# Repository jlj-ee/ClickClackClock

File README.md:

# ClickClackClock
This was a hobby project to create an impractically loud and large clock constructed from salvaged electromechanical seven-segment flip digits (also known as vane displays). To be slightly less obnoxious, the clock automatically sleeps in dark rooms, and wakes up with the correct time when exposed to light -- great for people who like to wake up with the dawn! 
<!--- The clock can also be put into a countdown/stopwatch mode, appropriate for games, New Year's Eve, the apocalypse, etc. --->

The [flip digits](http://www.scoretronics.com/components/Digits_Brochure.pdf) came from a retired aquatics scoreboard/timing system. The segments change position when current is pulsed through a magnetic coil. 

## Software
__Required dependencies:__

**_More info TBA_**

## CAD Contents
We designed custom 2-layer PCBs for this project using [Eagle](https://www.autodesk.com/products/eagle/overview) and fabbed them using [OSHPark](https://oshpark.com/), with all through-hole components for ease of assembly:
- __clock_driver_board:__ Drives a single digit, and can be daisy-chained together for as many digits as needed.
- __clock_motherboard:__ Slightly larger than the Arduino UNO but with the same microcontroller and pad layout for future shield compatibility. Integrates the standard DS1307 RTC on the board and controls the whole system - digit drivers, buttons, photoresistor, etc.
- __clock_system:__ Schematic that describes the overall system of PCBs and auxiliary components.

## Assembly
The digits are supported in a frame made from MDF. 

**_More info TBA_**

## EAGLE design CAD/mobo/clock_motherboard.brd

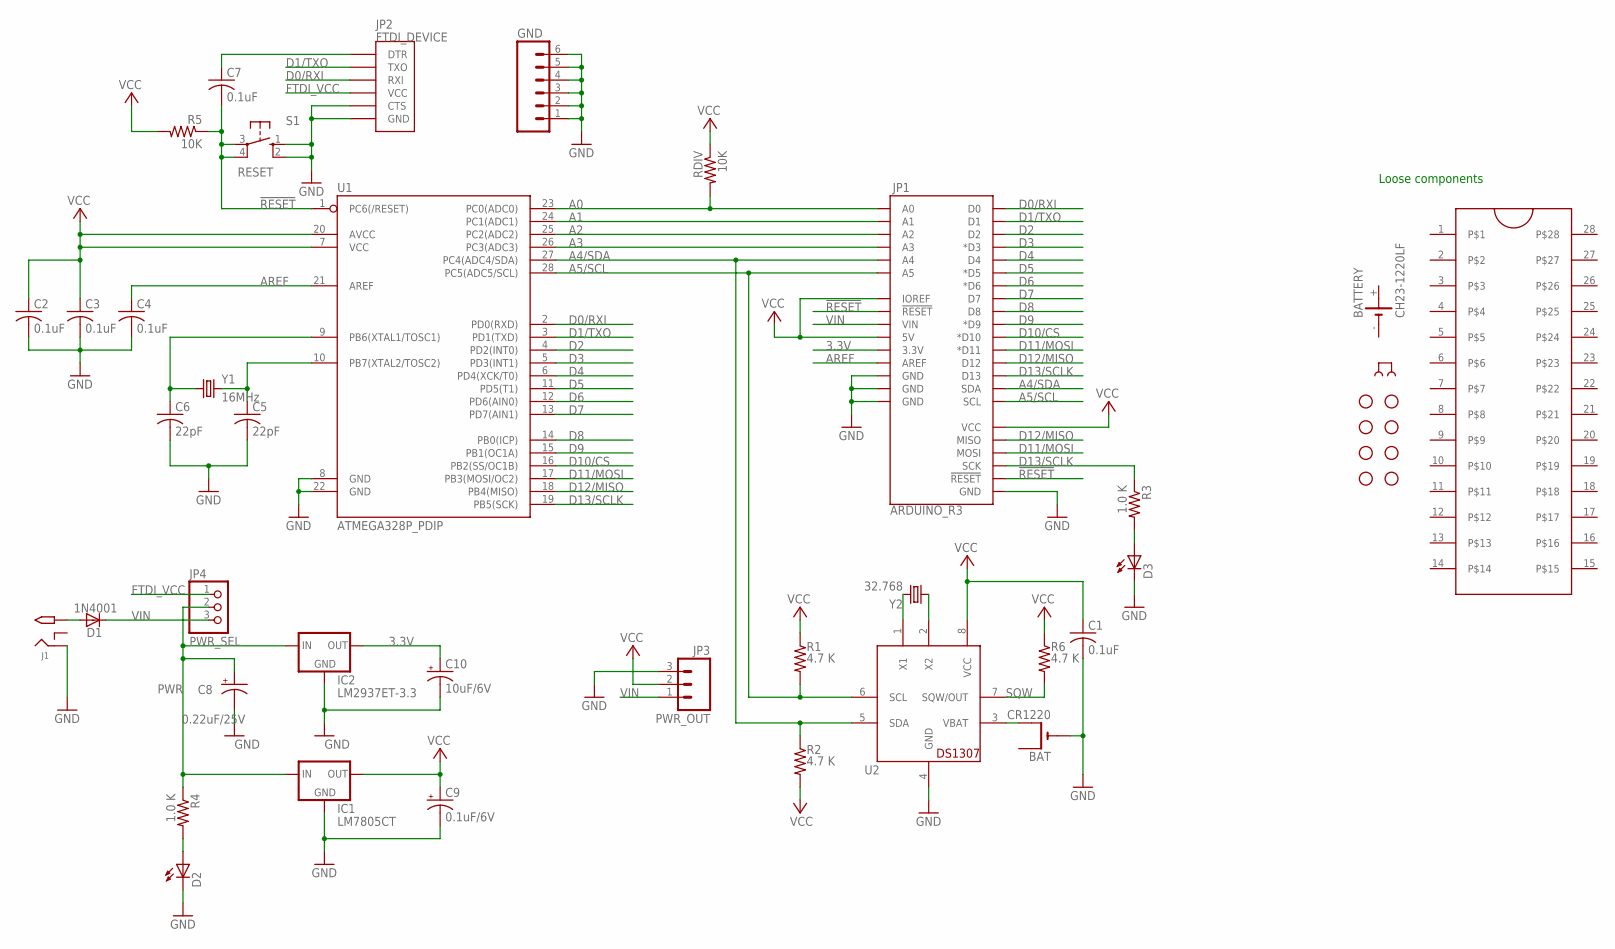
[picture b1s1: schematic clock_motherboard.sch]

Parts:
BAT: CR1220; CR1220-THM; PARTNO 3001
BATTERY: CH23-1220LF; PARTNO CR1220
C1, C2, C3, C4, C7: 0.1uF; C025-025X050; PARTNO 21RZ310-RC
C5, C6: 22pF; C025-025X050; PARTNO K220J15C0GF5TL2
C8: 0.22uF/25V; E2,5-6; PARTNO FG14X7R1H224KNT06
C9: 0.1uF/6V; E2,5-6; PARTNO 21RZ310-RC
C10: 10uF/6V; E2,5-6; PARTNO A758BG106M1EAAE070
D1: 1N4001; DO41-10; PARTNO 1N4001-TP
D2: RED; LED3MM; PARTNO WP7113SRD/D
D3: YELLOW; LED3MM; PARTNO WP7113SYD
GND: M06NO_SILK_FEMALE_PTH; 1X06_NO_SILK
IC1: LM7805CT; 78XXS; PARTNO LM7805CT/NOPB
IC2: LM2937ET-3.3; 78XXS; PARTNO LM2937ET-3.3/NOPB
J1: 2.1MMJACK; PJ-102A; PARTNO PJ-102AH
J2: PWR_SEL; JUMP; PARTNO 382811-8
JP1: ARDUINO_R3
JP2: FTDI_DEVICE; FTDI_DEVICE_SIDE; PARTNO 68000-406HLF
JP3: PWR_OUT; SCREWTERMINAL-3.5MM-3; PARTNO 1546551-3
JP4: PWR_SEL; 1X03; PARTNO 68001-403HLF
R1, R2, R6: 4.7 K; 0207/5V; PARTNO CFR-25JB-52-4K7
R3, R4: 1.0 K; 0207/5V; PARTNO CFR-25JB-52-1K
R5: 10K; 0207/5V; PARTNO CFR-25JB-52-10K
RDIV: 10K; 0207/5V; PARTNO CFR-25JB-52-10K
S1: RESET; B3F-10XX
SOCKET: ZIFSOCKET-28-3ZIFFSOCKET-28-3; DIL28-3-ZIF_SOCKET; PARTNO 4828-3004-CP
STANDOFF1, STANDOFF2, STANDOFF3, STANDOFF4: STAND-OFF; PARTNO 2200
STANDOFF5, STANDOFF6, STANDOFF7, STANDOFF8: STAND-OFF; PARTNO 9900
U1: ATMEGA328P_PDIP; DIL28-3; PARTNO ATMEGA328P-PU
U2: DS1307; DIL08; PARTNO DS1307+
Y1: 16MHz; HC49US; PARTNO HC49US-16.000MABJ-UB
Y2: 32.768; TC38H; PARTNO AB38T-32.768KHZ

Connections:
3.3V: C10.+, IC2.OUT, JP1.3.3V
!RESET: C7.2, JP1.RESET@1 (!RESET!), JP1.RESET@2 (!RESET!), R5.1, S1.3, S1.4 (P1), U1.1 (PC6(/RESET))
A0: JP1.A0, RDIV.2, U1.23 (PC0(ADC0))
A1: JP1.A1, U1.24 (PC1(ADC1))
A2: JP1.A2, U1.25 (PC2(ADC2))
A3: JP1.A3, U1.26 (PC3(ADC3))
A4/SDA: JP1.A4, JP1.SDA, R2.1, U1.27 (PC4(ADC4/SDA)), U2.5 (SDA)
A5/SCL: JP1.A5, JP1.SCL, R1.2, U1.28 (PC5(ADC5/SCL)), U2.6 (SCL)
AREF: C4.1, JP1.AREF, U1.21 (AREF)
D0/RXI: JP1.D0, JP2.P$3 (RXI), U1.2 (PD0(RXD))
D1/TXO: JP1.D1, JP2.P$2 (TXO), U1.3 (PD1(TXD))
D2: JP1.D2, U1.4 (PD2(INT0))
D3: JP1.D3 (*D3), U1.5 (PD3(INT1))
D4: JP1.D4, U1.6 (PD4(XCK/T0))
D5: JP1.D5 (*D5), U1.11 (PD5(T1))
D6: JP1.D6 (*D6), U1.12 (PD6(AIN0))
D7: JP1.D7, U1.13 (PD7(AIN1))
D8: JP1.D8, U1.14 (PB0(ICP))
D9: JP1.D9 (*D9), U1.15 (PB1(OC1A))
D10/CS: JP1.D10 (*D10), U1.16 (PB2(SS/OC1B))
D11/MOSI: JP1.D11 (*D11), JP1.MOSI, U1.17 (PB3(MOSI/OC2))
D12/MISO: JP1.D12, JP1.MISO, U1.18 (PB4(MISO))
D13/SCLK: JP1.D13, JP1.SCK, R3.1, U1.19 (PB5(SCK))
FTDI_VCC: JP2.P$4 (VCC), JP4.1
GND: BAT.-, C1.2, C2.2, C3.2, C4.2, C5.2, C6.2, C8.-, C9.-, C10.-, D2.K (C), D3.K (C), GND.1, GND.2, GND.3, GND.4, GND.5, GND.6, IC1.GND, IC2.GND, J1.RING, JP1.GND@1 (GND), JP1.GND@2 (GND), JP1.GND@3 (GND), JP1.GND@4 (GND), JP2.P$5 (CTS), JP2.P$6 (GND), JP3.3, S1.1 (S), S1.2 (S1), U1.8 (GND), U1.22 (GND), U2.4 (GND)
unnamed: C6.1, U1.9 (PB6(XTAL1/TOSC1)), Y1.1
unnamed: C5.1, U1.10 (PB7(XTAL2/TOSC2)), Y1.2
unnamed: C7.1, JP2.P$1 (DTR)
unnamed: D3.A, R3.2
unnamed: D2.A, R4.2
unnamed: U2.1 (X1), Y2.2
unnamed: U2.2 (X2), Y2.1
unnamed: D1.A, J1.TIP
unnamed: BAT.+2 (+1), U2.3 (VBAT)
PWR: C8.+, IC1.IN, IC2.IN, JP4.2, R4.1
SQW: R6.2, U2.7 (SQW/OUT)
VCC: C1.1, C2.1, C3.1, C9.+, IC1.OUT, JP1.5V, JP1.IOREF, JP1.VCC, JP3.2, R1.1, R2.2, R5.2, R6.1, RDIV.1, U1.7 (VCC), U1.20 (AVCC), U2.8 (VCC)
VIN: D1.C, JP1.VIN, JP3.1, JP4.3

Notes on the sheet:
Loose components

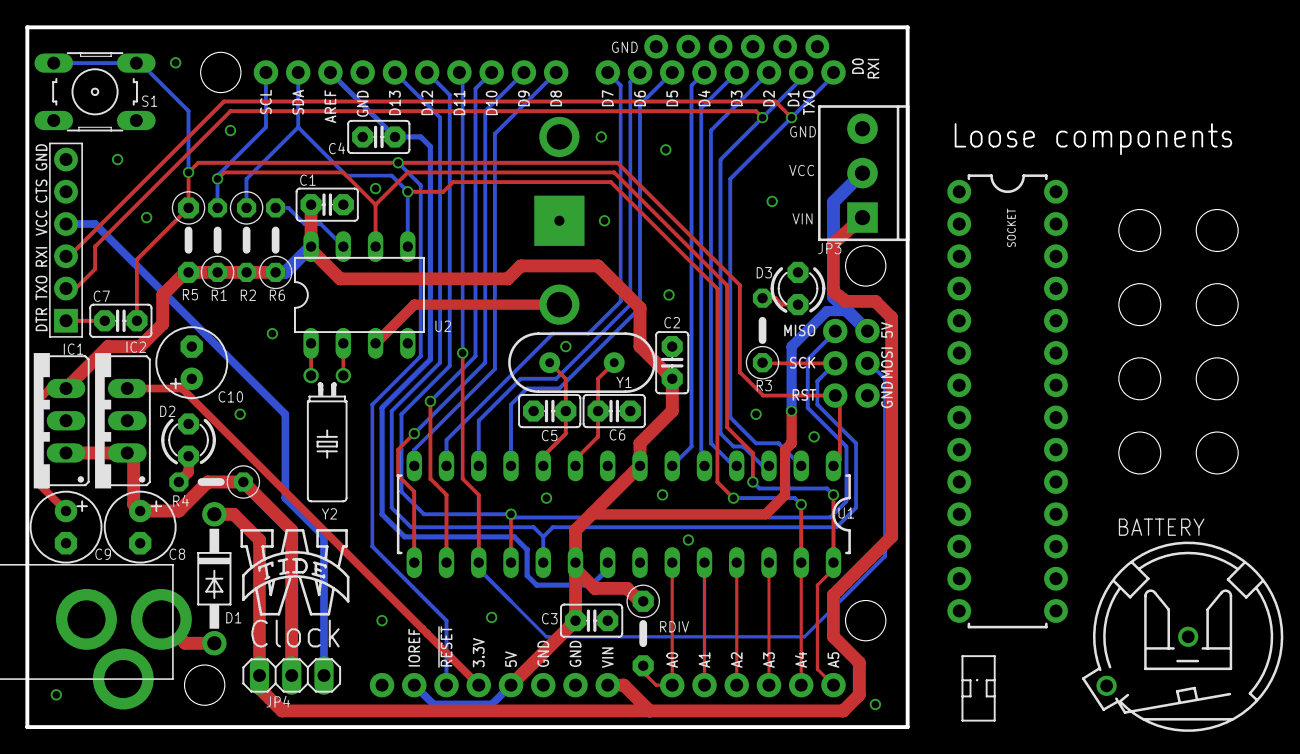
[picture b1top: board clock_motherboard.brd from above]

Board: 2 copper layers, 98.1 x 55.1 mm, 45 parts (1 on the bottom side), 38 nets.

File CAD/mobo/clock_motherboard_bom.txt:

Part	Value	Attributes	Package	Description	Part Num	Mfg Name	VID	Vendor Part Num	Description	Pkg Code	XREF
BAT	CR1220		CR1220-THM	CR1216/CR1220/CR1225 12mm 3V lithium coin cell	3001	Keystone Electronics	ME	534-3001	HOLDER BATTERY COIN 12MM DIA THM	*	REF14
BATTERY	CH23-1220LF		CH23-1220LF	Battary Holder, DIP, 12mm	CR1220	FDK America	ME	658-CR1220	BATTERY LITHIUM 3V COIN 12.5MM	*	REF15
C1	0.1uF		C025-025X050	CAPACITOR, American symbol	21RZ310-RC	Xicon	ME	21RZ310-RC	Multilayer Ceramic Capacitors MLCC - Leaded .1uF 50volts Z5U 20% 2.5mm L/S	*	REF5
C2	0.1uF		C025-025X050	CAPACITOR, American symbol	21RZ310-RC	Xicon	ME	21RZ310-RC	Multilayer Ceramic Capacitors MLCC - Leaded .1uF 50volts Z5U 20% 2.5mm L/S	*	REF5
C3	0.1uF		C025-025X050	CAPACITOR, American symbol	21RZ310-RC	Xicon	ME	21RZ310-RC	Multilayer Ceramic Capacitors MLCC - Leaded .1uF 50volts Z5U 20% 2.5mm L/S	*	REF5
C4	0.1uF		C025-025X050	CAPACITOR, American symbol	21RZ310-RC	Xicon	ME	21RZ310-RC	Multilayer Ceramic Capacitors MLCC - Leaded .1uF 50volts Z5U 20% 2.5mm L/S	*	REF5
C5	22pF		C025-025X050	CAPACITOR, American symbol	K220J15C0GF5TL2	Vishay / BC Components	ME	594-K220J15C0GF5TL2	Multilayer Ceramic Capacitors MLCC - Leaded 22pF 50volts 5% C0G 2.5mm LS	*	REF17
C6	22pF		C025-025X050	CAPACITOR, American symbol	K220J15C0GF5TL2	Vishay / BC Components	ME	594-K220J15C0GF5TL2	Multilayer Ceramic Capacitors MLCC - Leaded 22pF 50volts 5% C0G 2.5mm LS	*	REF17
C7	0.1uF		C025-025X050	CAPACITOR, American symbol	21RZ310-RC	Xicon	ME	21RZ310-RC	Multilayer Ceramic Capacitors MLCC - Leaded .1uF 50volts Z5U 20% 2.5mm L/S	*	REF5
C8	0.22uF/25V		E2,5-6	POLARIZED CAPACITOR, American symbol	FG14X7R1H224KNT06	TDK	ME	810-FG14X7R1H224KNT6	Multilayer Ceramic Capacitors MLCC - Leaded RAD 50V 0.22uF X7R 10% LS:2.5mm	*	REF20
C9	0.1uF/6V		E2,5-6	POLARIZED CAPACITOR, American symbol	21RZ310-RC	Xicon	ME	21RZ310-RC	Multilayer Ceramic Capacitors MLCC - Leaded .1uF 50volts Z5U 20% 2.5mm L/S	*	REF5
C10	10uF/6V		E2,5-6	POLARIZED CAPACITOR, American symbol	A758BG106M1EAAE070	Kemet	ME	80-A758BG106M1EAAE70	Aluminum Organic Polymer Capacitors 25volts 10uF 20% ESR=70 LS=2mm 5000hr	*	REF19
D1	1N4001		DO41-10	DIODE	1N4001-TP	Micro Commercial Co.	ME	833-1N4001-TP	DIODE GEN PURP 50V 1A DO41	*	REF21
D2	RED		LED3MM	LED	WP7113SRD/D	Kingbright	ME	604-WP7113SRD/D	Standard LEDs - Through Hole RED DIFFUSED	*	REF8
D3	YELLOW		LED3MM	LED	WP7113SYD	Kingbright	ME	604-WP7113SYD	Standard LEDs - Through Hole YELLOW DIFFUSED	*	REF16
IC1	LM7805CT		78XXS	VOLTAGE REGULATOR	LM7805CT/NOPB	Texas Instruments	ME	926-LM7805CT/NOPB	IC REG LINEAR 5.0V 1A TO220-3	*	REF12
IC2	LM2937ET-3.3		78XXS	VOLTAGE REGULATOR	LM2937ET-3.3/NOPB	Texas Instruments	ME	926-LM2937ET-3.3NOPB	IC REG LINEAR 3.3V 0.5A TO220-3	*	REF13
J1	2.1MMJACK		PJ-102A		PJ-102AH	CUI Inc.	ME	490-PJ-102AH	CONN PWR JACK 2X5.5MM SOLDER	*	REF27
J2	PWR_SEL		JUMP	JUMPER header	382811-8	TE Connectivity	ME	571-3828118	SHUNT, ECON, PHBR 5AU, BLACK	*	REF31
JP2	FTDI_DEVICE		FTDI_DEVICE_SIDE	Connector which mates to FTDI basic or FTDI cable.	68000-406HLF	Amphenol FCI	ME	649-68000-406HLF	CONN HEADER 6 POS .100	*	REF30
JP3	PWR_OUT		SCREWTERMINAL-3.5MM-3	Header 3	1546551-3	TE Connectivity	ME	571-1546551-3	Fixed Terminal Blocks 3P,STRAIGHT SIDE ENTRY,3.5MM	*	REF3
JP4	PWR_SEL		1X03	PIN HEADER	68001-403HLF	Amphenol FCI	ME	649-68001-403HLF	CONN HEADER 3 POS .100	*	REF29
R1	4.7 K		0207/5V	RESISTOR, American symbol	CFR-25JB-52-4K7	Yageo	ME	603-CFR-25JB-52-4K7	Carbon Film Resistors - Through Hole Carbon Film Resistors - Through Hole 4.7kohm 1/4W 5%	*	REF24
R2	4.7 K		0207/5V	RESISTOR, American symbol	CFR-25JB-52-4K7	Yageo	ME	603-CFR-25JB-52-4K7	Carbon Film Resistors - Through Hole Carbon Film Resistors - Through Hole 4.7kohm 1/4W 5%	*	REF24
R3	1.0 K		0207/5V	RESISTOR, American symbol	CFR-25JB-52-1K	Yageo	ME	603-CFR-25JB-1K0	Carbon Film Resistors - Through Hole Carbon Film Resistors - Through Hole 1kohm 1/4W 5%	*	REF23
R4	1.0 K		0207/5V	RESISTOR, American symbol	CFR-25JB-52-1K	Yageo	ME	603-CFR-25JB-1K0	Carbon Film Resistors - Through Hole Carbon Film Resistors - Through Hole 1kohm 1/4W 5%	*	REF23
R5	10K		0207/5V	RESISTOR, American symbol	CFR-25JB-52-10K	Yageo	ME	603-CFR-25JB-52-10K	Carbon Film Resistors - Through Hole Carbon Film Resistors - Through Hole 10kohm 1/4W 5%	*	REF25
R6	4.7 K		0207/5V	RESISTOR, American symbol	CFR-25JB-52-4K7	Yageo	ME	603-CFR-25JB-52-4K7	Carbon Film Resistors - Through Hole Carbon Film Resistors - Through Hole 4.7kohm 1/4W 5%	*	REF24
RDIV	10K		0207/5V	RESISTOR, American symbol	CFR-25JB-52-10K	Yageo	ME	603-CFR-25JB-52-10K	Carbon Film Resistors - Through Hole Carbon Film Resistors - Through Hole 10kohm 1/4W 5%	*	REF25
S1	RESET		B3F-10XX	OMRON SWITCH	B3F-1000	Omron Electronics	ME	653-B3F-1000	Tactile Switches 6X6 Flat 4.3mm Btn Force 100g w/o Grd	*	REF28
SOCKET	ZIFSOCKET-28-3ZIFFSOCKET-28-3		DIL28-3-ZIF_SOCKET	Lever-action ZIF socket for 28-pin ICs	4828-3004-CP	3M	ME	517-4828-3004-CP	IC & Component Sockets SOCKET 28POS .3"" IC OPEN FRAME	*	REF10
STANDOFF1	STAND-OFF		STAND-OFF	#4 Stand Off	2200	Keystone Electronics	ME	534-2201	Standoffs & Spacers HEX .250X.250 ALUM	*	REF33
STANDOFF2	STAND-OFF		STAND-OFF	#4 Stand Off	2200	Keystone Electronics	ME	534-2201	Standoffs & Spacers HEX .250X.250 ALUM	*	REF33
STANDOFF3	STAND-OFF		STAND-OFF	#4 Stand Off	2200	Keystone Electronics	ME	534-2201	Standoffs & Spacers HEX .250X.250 ALUM	*	REF33
STANDOFF4	STAND-OFF		STAND-OFF	#4 Stand Off	2200	Keystone Electronics	ME	534-2201	Standoffs & Spacers HEX .250X.250 ALUM	*	REF33
STANDOFF5	STAND-OFF		STAND-OFF	#4 Stand Off	9900	Keystone Electronics	ME	534-9900	Screws & Fasteners 4-40 X 1/4 SCREW	*	REF32
STANDOFF6	STAND-OFF		STAND-OFF	#4 Stand Off	9900	Keystone Electronics	ME	534-9900	Screws & Fasteners 4-40 X 1/4 SCREW	*	REF32
STANDOFF7	STAND-OFF		STAND-OFF	#4 Stand Off	9900	Keystone Electronics	ME	534-9900	Screws & Fasteners 4-40 X 1/4 SCREW	*	REF32
STANDOFF8	STAND-OFF		STAND-OFF	#4 Stand Off	9900	Keystone Electronics	ME	534-9900	Screws & Fasteners 4-40 X 1/4 SCREW	*	REF32
U1	ATMEGA328P_PDIP		DIL28-3	uC used in the Arduino	ATMEGA328P-PU	Microchip Technology / Atmel	ME	556-ATMEGA328P-PU	8-bit Microcontrollers - MCU 32KB In-system Flash 20MHz 1.8V-5.5V	*	REF9
U2	DS1307		DIL08	DS1307	DS1307+	Maxim Integrated	ME	700-DS1307	Real Time Clock 64x8 Serial I2C RTC	*	REF11
Y1	16MHz		HC49US	Various standard crystals. Proven footprints.	HC49US-16.000MABJ-UB	Citizen FineDevice	ME	695-HC49US-16-U	Crystals 16MHz 18pF HC49S THROUGH HOLE	*	REF26
Y2	32.768		TC38H	CRYSTAL	AB38T-32.768KHZ	Abracon LLC	ME	815-AB38T-32.768KHZ	CRYSTAL 32.7680KHZ 12.5PF T/H	*	REF22

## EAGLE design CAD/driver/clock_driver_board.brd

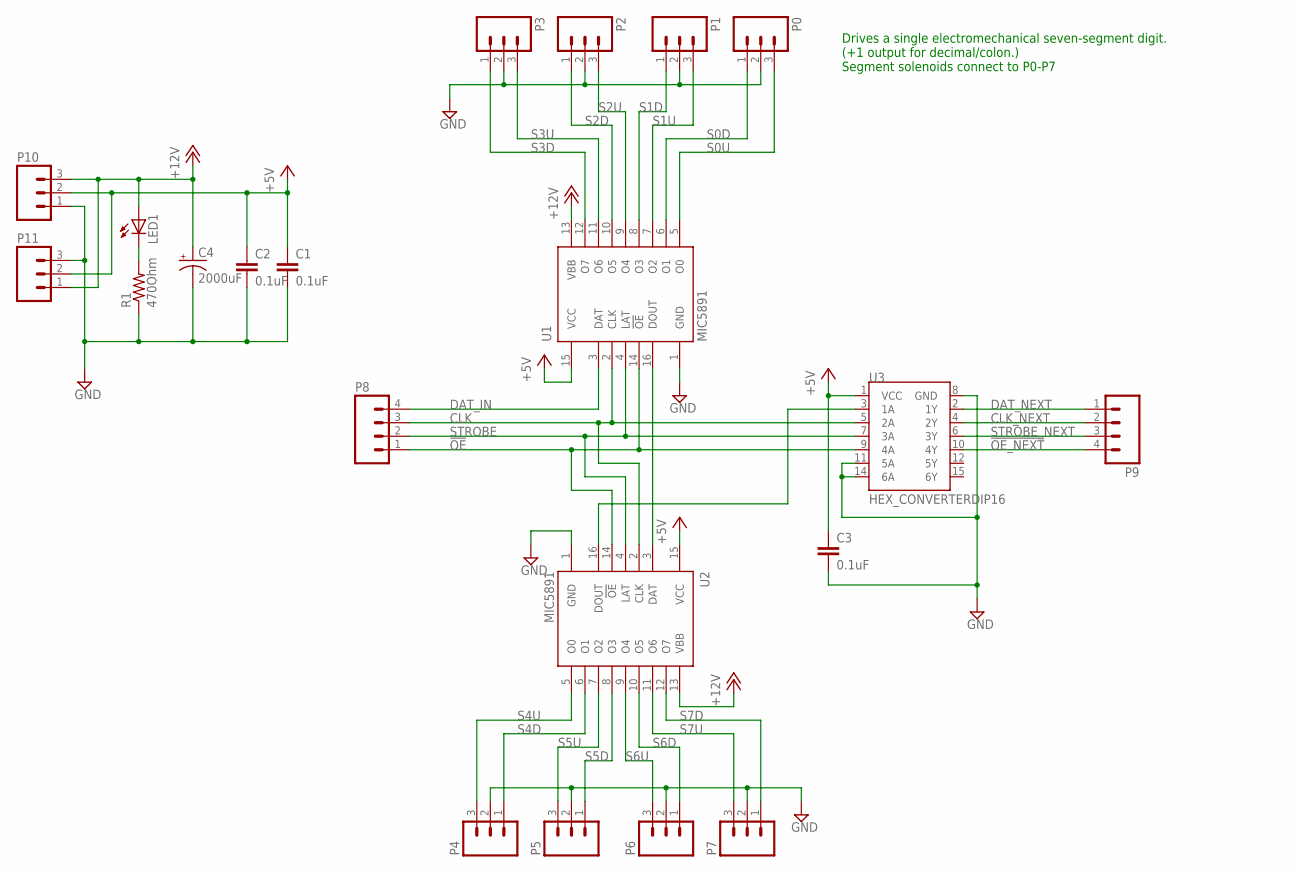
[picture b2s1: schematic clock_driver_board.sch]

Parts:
C1, C2, C3: 0.1uF; C2.5-2; PARTNO 21RZ310-RC
C4: 2000uF; E7,5-16; PARTNO EEU-TP1E202S
LED1: LED3MM; PARTNO WP7113SRD/D
P0, P1, P2, P3, P4, P5, P6, P7: M03LONGPADS; 1X03_LONGPADS
P8, P9: M04LONGPADS; 1X04_LONGPADS; PARTNO 826631-4
P10, P11: M03SCREW; SCREWTERMINAL-3.5MM-3; PARTNO 1546551-3
R1: 470Ohm; 0204/7; PARTNO CFR-25JR-52-470R
U1, U2: MIC5891; DIL16; PARTNO MIC5891YN
U3: HEX_CONVERTERDIP16; DIL16; PARTNO CD74HC4050E

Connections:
!OE: P8.1, U1.14 (!OE), U2.14 (!OE), U3.9 (4A)
!OE_NEXT: P9.4, U3.10 (4Y)
+5V: C1.1, C2.1, C3.1, P10.2, P11.2, U1.15 (VCC), U2.15 (VCC), U3.1 (VCC)
+12V: C4.+, LED1.A, P10.3, P11.1, U1.13 (VBB), U2.13 (VBB)
CLK: P8.3, U1.2 (CLK), U2.2 (CLK), U3.5 (2A)
CLK_NEXT: P9.2, U3.4 (2Y)
DAT_IN: P8.4, U1.3 (DAT)
DAT_NEXT: P9.1, U3.2 (1Y)
GND: C1.2, C2.2, C3.2, C4.-, P0.2, P1.2, P2.2, P3.2, P4.2, P5.2, P6.2, P7.2, P10.1, P11.3, R1.1, U1.1 (GND), U2.1 (GND), U3.8 (GND), U3.11 (5A), U3.14 (6A)
LEDR: LED1.K (C), R1.2
unnamed: U1.16 (DOUT), U2.3 (DAT)
unnamed: U2.16 (DOUT), U3.3 (1A)
S0D: P0.1, U1.6 (O1)
S0U: P0.3, U1.5 (O0)
S1D: P1.1, U1.8 (O3)
S1U: P1.3, U1.7 (O2)
S2D: P2.1, U1.10 (O5)
S2U: P2.3, U1.9 (O4)
S3D: P3.1, U1.12 (O7)
S3U: P3.3, U1.11 (O6)
S4D: P4.1, U2.6 (O1)
S4U: P4.3, U2.5 (O0)
S5D: P5.1, U2.8 (O3)
S5U: P5.3, U2.7 (O2)
S6D: P6.1, U2.10 (O5)
S6U: P6.3, U2.9 (O4)
S7D: P7.1, U2.12 (O7)
S7U: P7.3, U2.11 (O6)
STROBE: P8.2, U1.4 (LAT), U2.4 (LAT), U3.7 (3A)
STROBE_NEXT: P9.3, U3.6 (3Y)

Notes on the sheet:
Drives a single electromechanical seven-segment digit. (+1 output for decimal/colon.) Segment solenoids connect to P0-P7

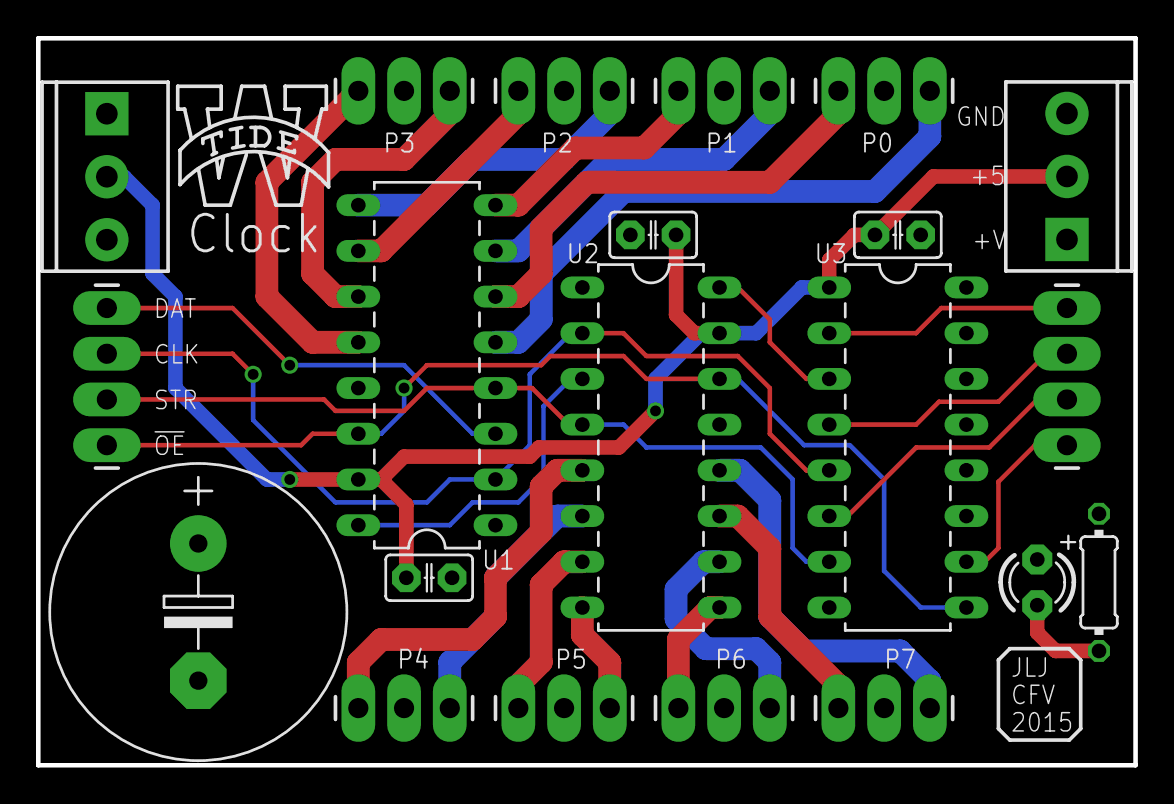
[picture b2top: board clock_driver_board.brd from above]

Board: 2 copper layers, 61.0 x 40.4 mm, 21 parts (0 on the bottom side), 30 nets.

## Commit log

2018-01-25 Adding CAD files
2018-01-25 Moving CAD files to subdirectory
2018-01-25 Removing old CAD files
2018-01-25 Adding preliminary code
2018-01-28 Update clk_main.ino
    Updated. Not sure if anything changed. But it's current as of today.
2018-01-28 Update shift.ino
    I don't think there were any changes
2018-01-28 I MOVED THE FILES. USING GIT BASH ON WINDOWS. TAKE THAT.
2018-01-29 Adding gitignore file
2018-01-29 Minor updates to README
2018-01-29 Fixing gitignore
2018-01-29 Ignoring Eagle auto-backups
2018-01-29 Updating motherboard CAD files (OSHpark version)
2018-01-29 README improvements
2018-01-29 Updated driver board CAD files for BOM
2018-01-30 Adding updated part database and motherboard BOM, closes #4
2018-01-31 Updated gitignore
2018-02-01 Adding full-system schematic, closes #5
2018-02-01 Minor readme updates
2018-02-01 Adding MIT license
2018-02-05 Started refactoring code to use new class
2018-02-05 Minor changes
2018-02-05 Fixed mobo power circuit and updated BOM
2018-02-06 Updated environment for proper linting
2018-02-12 Updating workspace files
2018-02-12 Continued refactoring. Commiting before file rename
2018-02-12 Renamed files and directory. No code changes
2018-02-12 Fixes to account for renaming
2018-02-13 Renamed Code to src for consistency
2018-02-13 Cleaned up SerialClock and added doxygen-style comments to header
2018-02-13 One more rename...
2018-02-14 Updates to account for file rename and new documentation.
2018-02-20 Added display buffer and other code improvements.
2018-03-08 Adding external dependencies as git submodules
2018-03-08 Added display buffer and optimized bit-bang serial
2018-03-18 Significant changes to SerialClockDisplay to fix bugs found in hardware testing. Skeleton code added for timekeeping to main sketch.

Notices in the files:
parts and their libraries:
SparkFun-Connectors: Licensing: Creative Commons ShareAlike 4.0 International - https://creativecommons.org/licenses/by-sa/4.0
random: This is v1 and is licensed under the Creative Commons (Attribution-Non-Commercial-Share Alike 2.0 UK)
